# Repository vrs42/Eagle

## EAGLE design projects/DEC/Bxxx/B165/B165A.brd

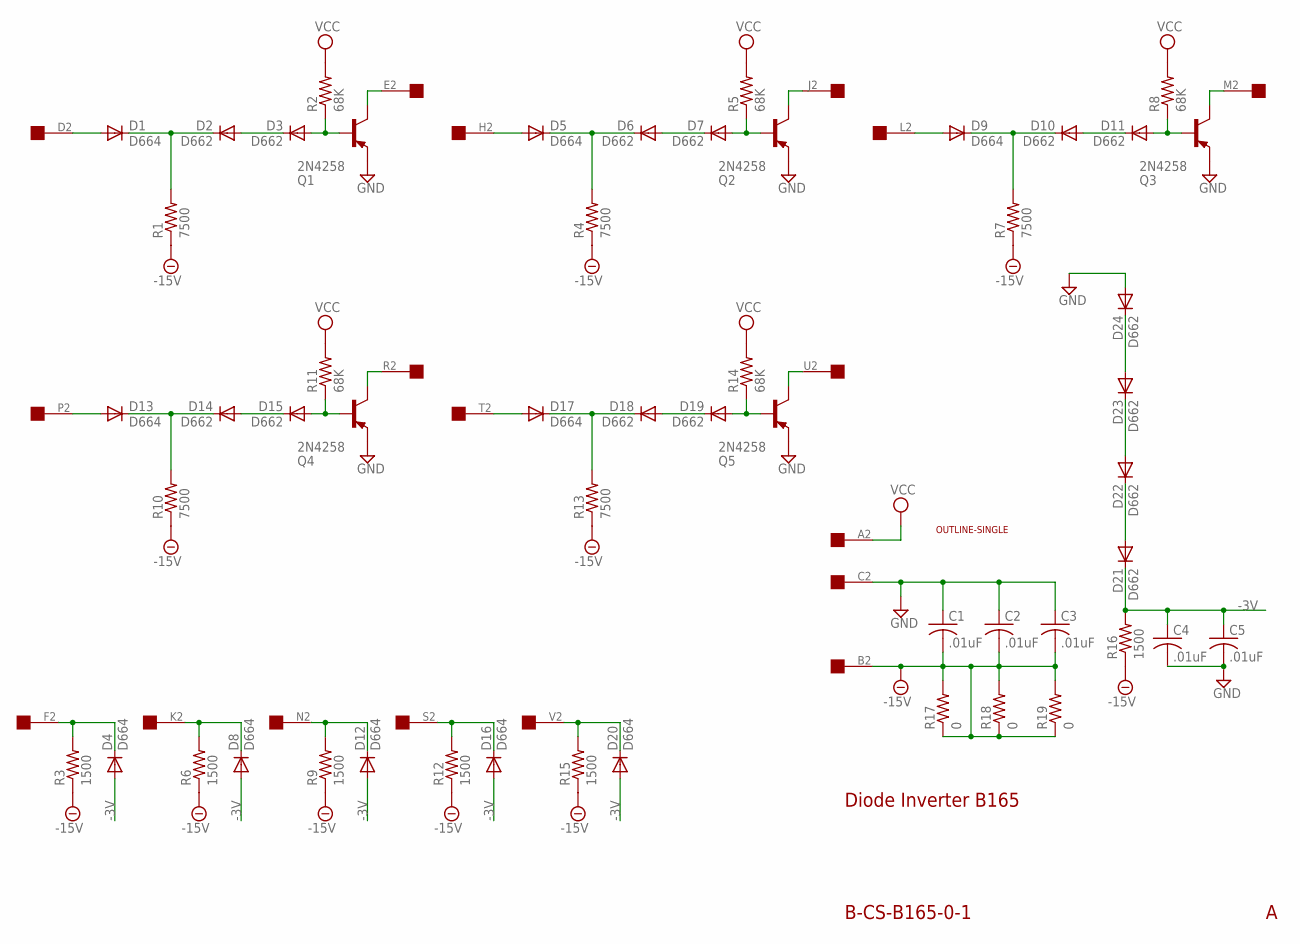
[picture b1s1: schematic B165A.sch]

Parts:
C1, C2, C3, C4, C5: .01uF; C063-025X075
D1, D4, D5, D8, D9, D12, D13, D16, D17, D20: D664; DO35-10
D2, D3, D6, D7, D10, D11, D14, D15, D18, D19, D21, D22, D23, D24: D662; DO35-10
Q1, Q2, Q3, Q4, Q5: 2N4258; TO5
R1, R4, R7, R10, R13: 7500; 0207/10
R2, R5, R8, R11, R14: 68K; 0207/10
R3, R6, R9, R12, R15, R16: 1500; 0207/10
R17, R18, R19: 0; 0207/10
U$1: OUTLINE-SINGLE; SINGLE
U$2: EDGE-1; EDGE-CON1

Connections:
-3V: C4.1, C5.1, D4.A, D8.A, D12.A, D16.A, D20.A, D21.C, R16.2
-15V: C1.2, C2.2, C3.2, R1.1, R3.1, R4.1, R6.1, R7.1, R9.1, R10.1, R12.1, R13.1, R15.1, R16.1, R17.1, R17.2, R18.1, R18.2, R19.1, R19.2, U$2.B2
GND: C1.1, C2.1, C3.1, C4.2, C5.2, D24.A, Q1.1 (E), Q2.1 (E), Q3.1 (E), Q4.1 (E), Q5.1 (E), U$2.C2
unnamed: D1.A, U$2.D2
unnamed: D1.C, D2.C, R1.2
unnamed: D2.A, D3.C
unnamed: D16.C, R12.2, U$2.S2
unnamed: D3.A, Q1.2 (B), R2.1
unnamed: Q1.3 (C), U$2.E2
unnamed: D4.C, R3.2, U$2.F2
unnamed: D8.C, R6.2, U$2.K2
unnamed: D12.C, R9.2, U$2.N2
unnamed: D5.A, U$2.H2
unnamed: D5.C, D6.C, R4.2
unnamed: D6.A, D7.C
unnamed: D17.A, U$2.T2
unnamed: D7.A, Q2.2 (B), R5.1
unnamed: Q2.3 (C), U$2.J2
unnamed: D9.A, U$2.L2
unnamed: D9.C, D10.C, R7.2
unnamed: D10.A, D11.C
unnamed: D17.C, D18.C, R13.2
unnamed: D11.A, Q3.2 (B), R8.1
unnamed: Q3.3 (C), U$2.M2
unnamed: D13.A, U$2.P2
unnamed: D13.C, D14.C, R10.2
unnamed: D14.A, D15.C
unnamed: D18.A, D19.C
unnamed: D15.A, Q4.2 (B), R11.1
unnamed: Q4.3 (C), U$2.R2
unnamed: D23.A, D24.C
unnamed: D22.A, D23.C
unnamed: D19.A, Q5.2 (B), R14.1
unnamed: D21.A, D22.C
unnamed: Q5.3 (C), U$2.U2
unnamed: D20.C, R15.2, U$2.V2
VCC: R2.2, R5.2, R8.2, R11.2, R14.2, U$2.A2

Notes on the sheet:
B-CS-B165-0-1
Diode Inverter B165

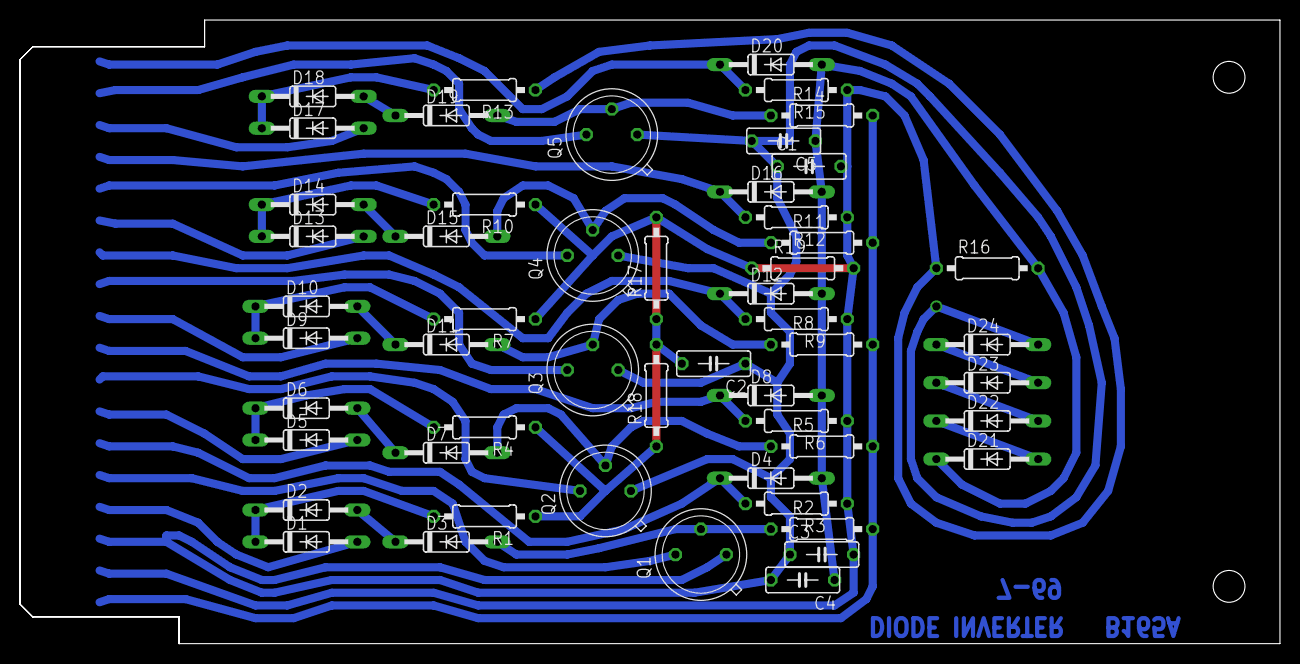
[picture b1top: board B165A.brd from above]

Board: 2 copper layers, 125.7 x 62.2 mm, 55 parts (0 on the bottom side), 37 nets.

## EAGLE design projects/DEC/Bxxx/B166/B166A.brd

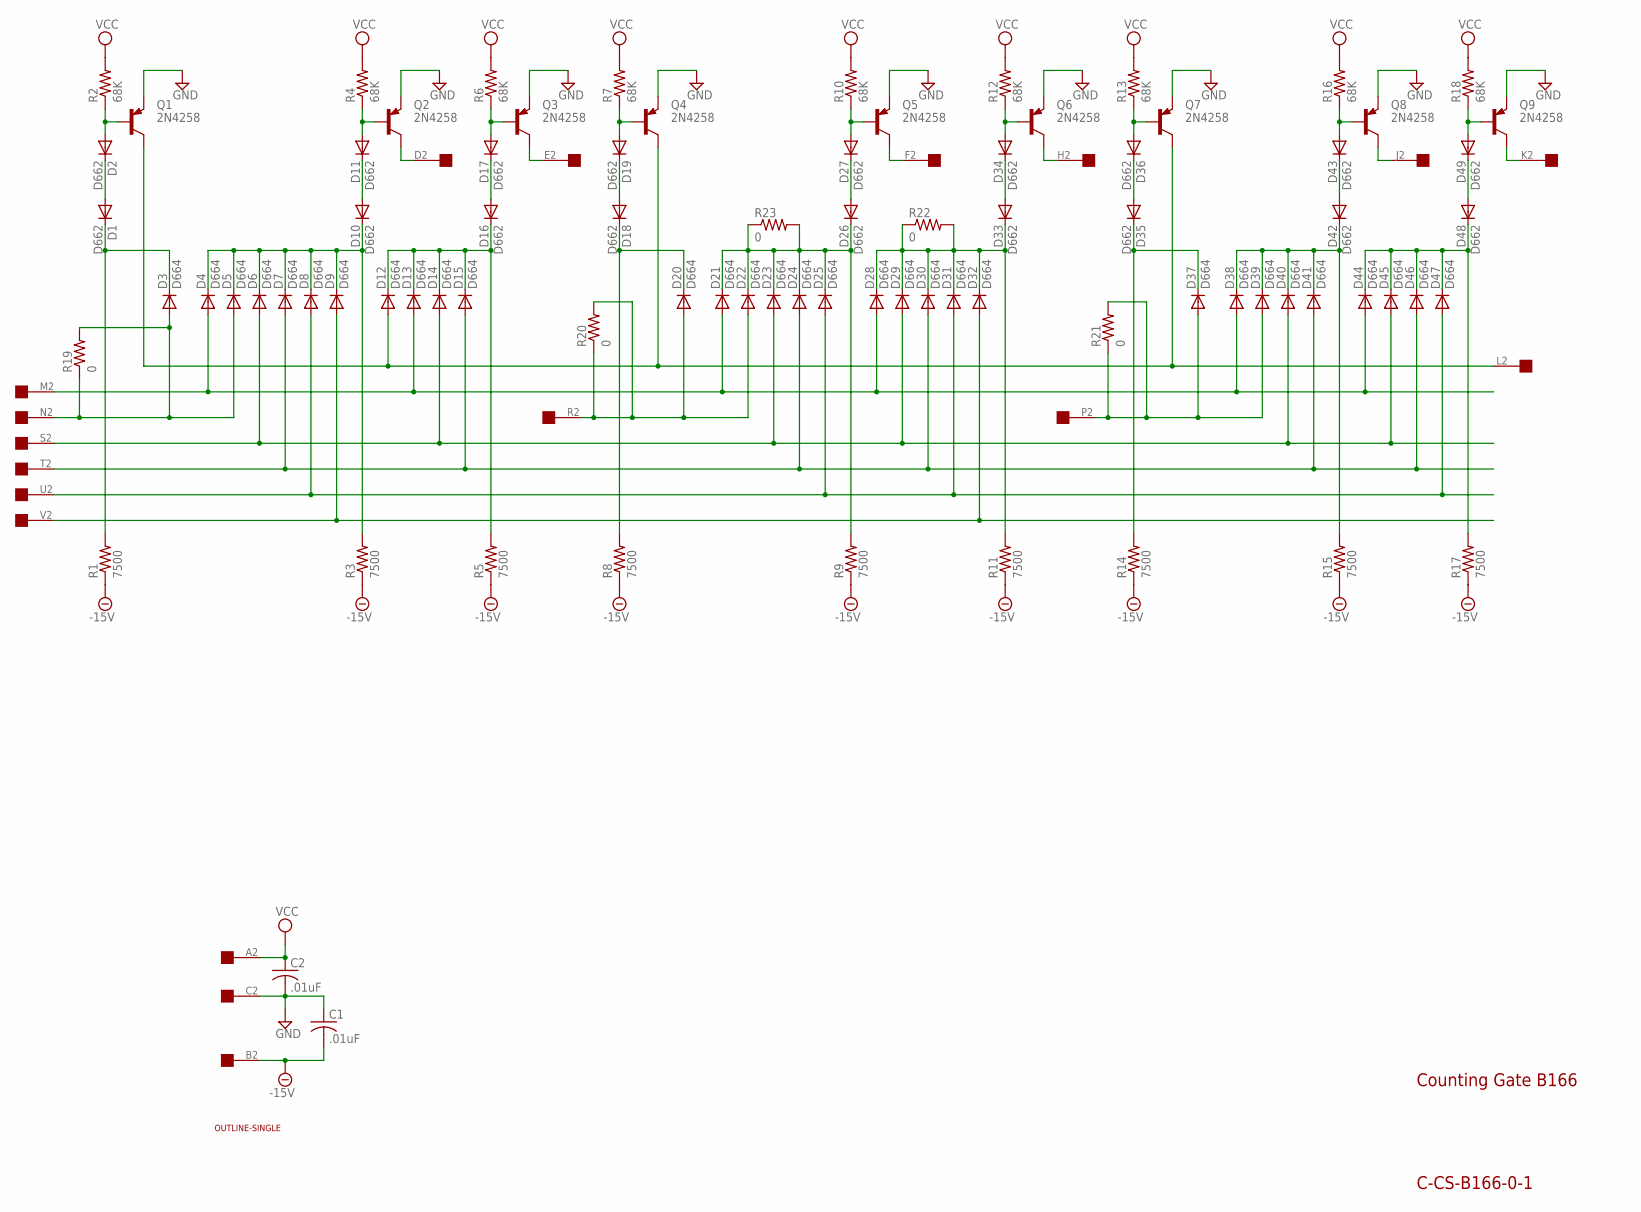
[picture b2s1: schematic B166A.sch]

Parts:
C1, C2: .01uF; C063-025X075
D1, D2, D10, D11, D16, D17, D18, D19, D26, D27, D33, D34, D35, D36, D42, D43, D48, D49: D662; DO35-10
D3, D4, D5, D6, D7, D8, D9, D12, D13, D14, D15, D20, D21, D22, D23, D24, D25, D28, D29, D30, D31, D32, D37, D38, D39, D40, D41, D44, D45, D46, D47: D664; DO35-10
Q1, Q2, Q3, Q4, Q5, Q6, Q7, Q8, Q9: 2N4258; TO5
R1, R3, R5, R8, R9, R11, R14, R15, R17: 7500; 0207/10
R2, R4, R6, R7, R10, R12, R13, R16, R18: 68K; 0207/10
R19, R20, R21, R22, R23: 0; 0207/10
U$1: OUTLINE-SINGLE; SINGLE
U$2: EDGE-1; EDGE-CON1

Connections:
-15V: C1.2, R1.1, R3.1, R5.1, R8.1, R9.1, R11.1, R14.1, R15.1, R17.1, U$2.B2
GND: C1.1, C2.2, Q1.1 (E), Q2.1 (E), Q3.1 (E), Q4.1 (E), Q5.1 (E), Q6.1 (E), Q7.1 (E), Q8.1 (E), Q9.1 (E), U$2.C2
unnamed: D2.A, Q1.2 (B), R2.1
unnamed: D1.A, D2.C
unnamed: D1.C, D3.C, R1.2
unnamed: D3.A, D5.A, R19.1, R19.2, U$2.N2
unnamed: D4.C, D5.C, D6.C, D7.C, D8.C, D9.C, D10.C, R3.2
unnamed: D12.A, Q1.3 (C), Q4.3 (C), Q7.3 (C), U$2.L2
unnamed: D4.A, D13.A, D21.A, D28.A, D38.A, D44.A, U$2.M2
unnamed: D8.A, D25.A, D31.A, D47.A, U$2.U2
unnamed: D7.A, D15.A, D24.A, D30.A, D41.A, D46.A, U$2.T2
unnamed: D11.A, Q2.2 (B), R4.1
unnamed: D9.A, D32.A, U$2.V2
unnamed: D6.A, D14.A, D23.A, D29.A, D40.A, D45.A, U$2.S2
unnamed: D10.A, D11.C
unnamed: Q2.3 (C), U$2.D2
unnamed: D19.A, Q4.2 (B), R7.1
unnamed: D12.C, D13.C, D14.C, D15.C, D16.C, R5.2
unnamed: D18.A, D19.C
unnamed: D18.C, D20.C, R8.2
unnamed: D20.A, D22.A, R20.1, R20.2, U$2.R2
unnamed: D21.C, D22.C, D23.C, D24.C, D25.C, D26.C, R9.2, R23.1, R23.2
unnamed: D17.A, Q3.2 (B), R6.1
unnamed: D16.A, D17.C
unnamed: Q3.3 (C), U$2.E2
unnamed: D27.A, Q5.2 (B), R10.1
unnamed: D26.A, D27.C
unnamed: Q5.3 (C), U$2.F2
unnamed: D28.C, D29.C, D30.C, D31.C, D32.C, D33.C, R11.2, R22.1, R22.2
unnamed: D34.A, Q6.2 (B), R12.1
unnamed: D33.A, D34.C
unnamed: Q6.3 (C), U$2.H2
unnamed: D36.A, Q7.2 (B), R13.1
unnamed: D35.A, D36.C
unnamed: D35.C, D37.C, R14.2
unnamed: D37.A, D39.A, R21.1, R21.2, U$2.P2
unnamed: D38.C, D39.C, D40.C, D41.C, D42.C, R15.2
unnamed: D43.A, Q8.2 (B), R16.1
unnamed: D42.A, D43.C
unnamed: Q8.3 (C), U$2.J2
unnamed: D44.C, D45.C, D46.C, D47.C, D48.C, R17.2
unnamed: D49.A, Q9.2 (B), R18.1
unnamed: D48.A, D49.C
unnamed: Q9.3 (C), U$2.K2
VCC: C2.1, R2.2, R4.2, R6.2, R7.2, R10.2, R12.2, R13.2, R16.2, R18.2, U$2.A2

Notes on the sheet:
C-CS-B166-0-1
Counting Gate B166

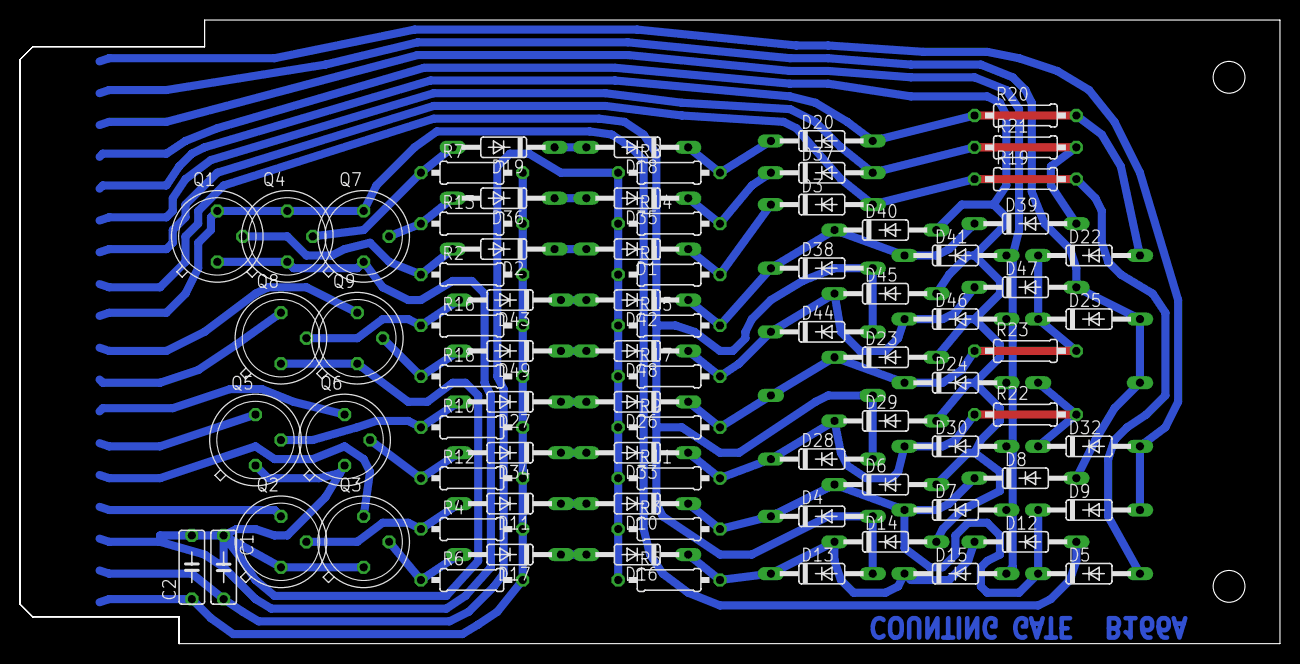
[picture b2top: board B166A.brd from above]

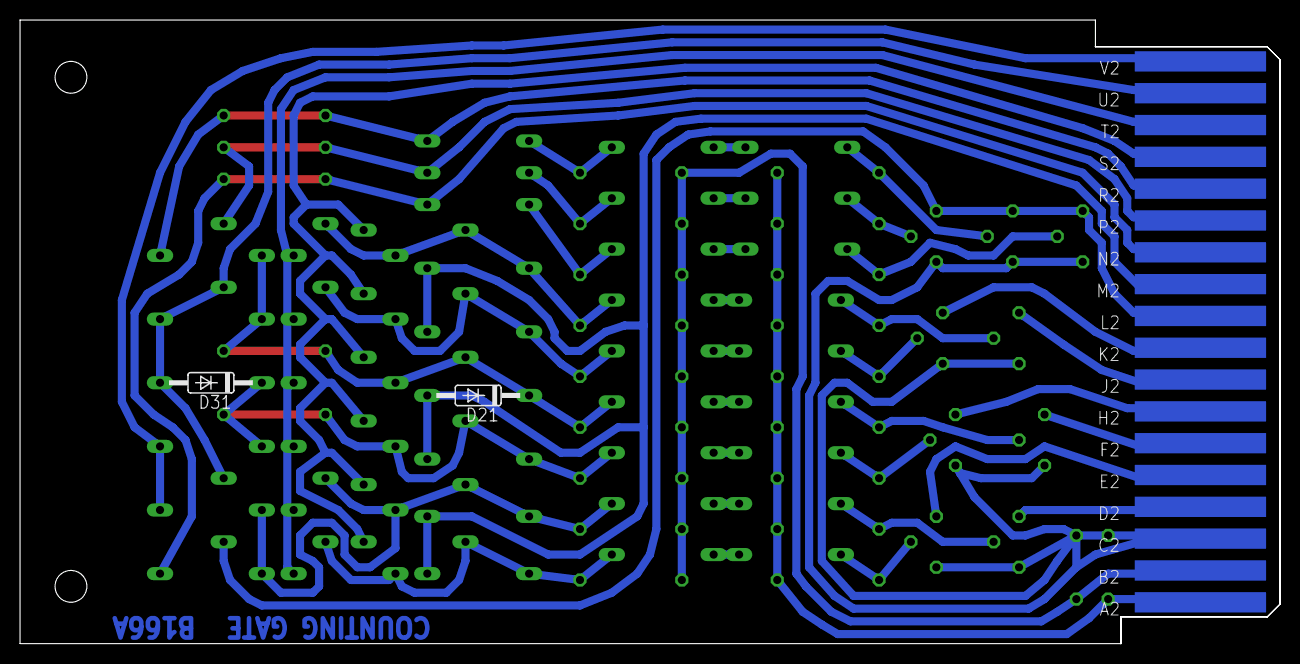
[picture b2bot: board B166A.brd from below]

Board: 2 copper layers, 125.7 x 62.2 mm, 85 parts (2 on the bottom side), 45 nets.

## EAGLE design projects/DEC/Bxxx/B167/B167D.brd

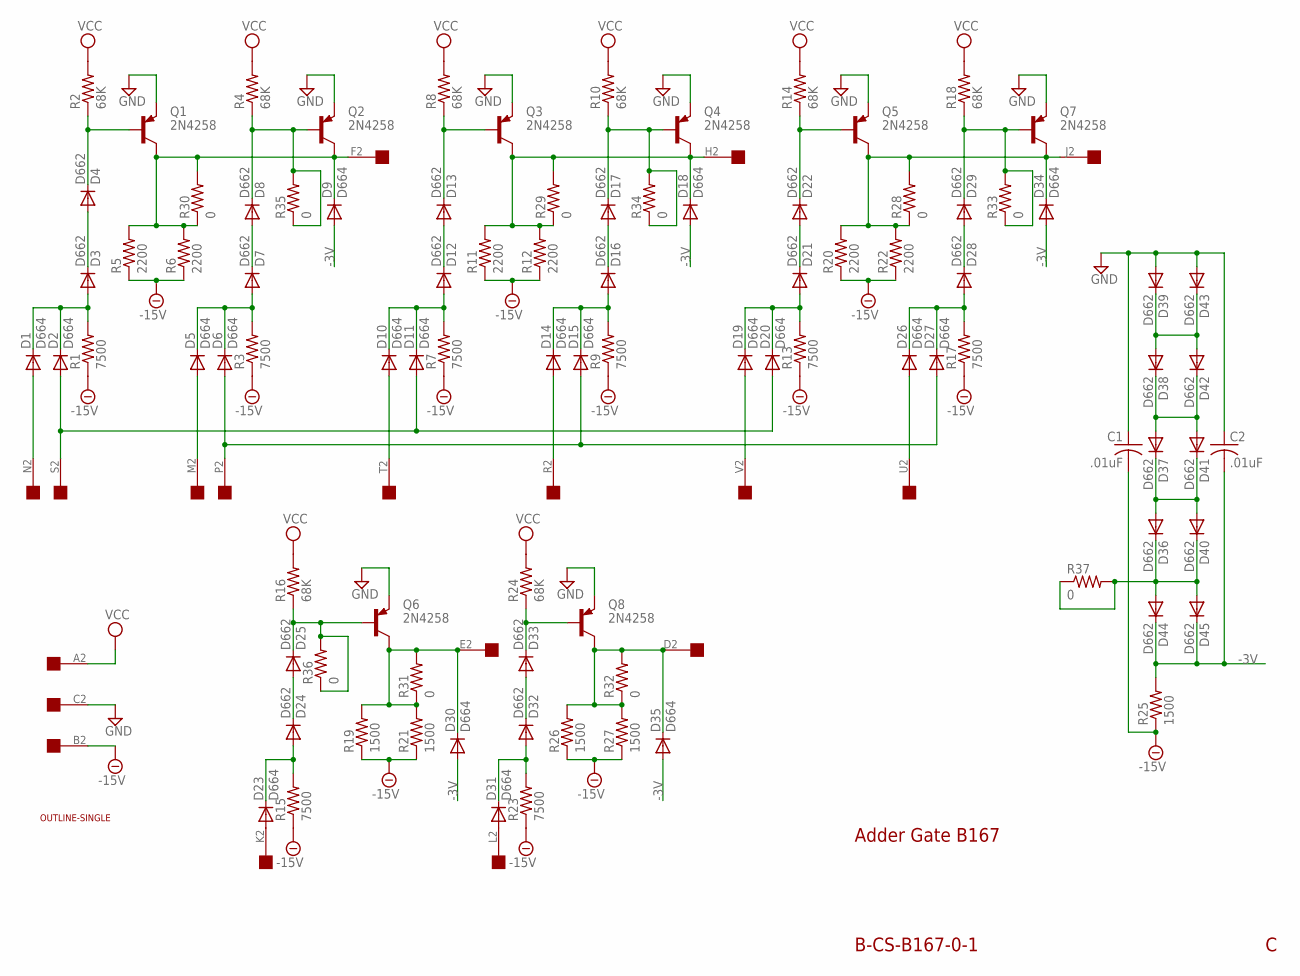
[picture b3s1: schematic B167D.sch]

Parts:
C1, C2: .01uF; C063-025X075
D1, D2, D5, D6, D9, D10, D11, D14, D15, D18, D19, D20, D23, D26, D27, D30, D31, D34, D35: D664; DO35-10
D3, D4, D7, D8, D12, D13, D16, D17, D21, D22, D24, D25, D28, D29, D32, D33, D36, D37, D38, D39, D40, D41, D42, D43, D44, D45: D662; DO35-10
Q1, Q2, Q3, Q4, Q5, Q6, Q7, Q8: 2N4258; TO5
R1, R3, R7, R9, R13, R15, R17, R23: 7500; 0207/10
R2, R4, R8, R10, R14, R16, R18, R24: 68K; 0207/10
R5, R6, R11, R12, R20, R22: 2200; 0207/10
R19, R21, R25, R26, R27: 1500; 0207/10
R28, R29, R30, R31, R32, R33, R34, R35, R36, R37: 0; 0207/10
U$1: OUTLINE-SINGLE; SINGLE
U$2: EDGE-1; EDGE-CON1

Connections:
-3V: C2.2, D9.A, D18.A, D30.A, D34.A, D35.A, D44.C, D45.C, R25.2
-15V: C1.2, R1.1, R3.1, R5.1, R6.1, R7.1, R9.1, R11.1, R12.1, R13.1, R15.1, R17.1, R19.1, R20.1, R21.1, R22.1, R23.1, R25.1, R26.1, R27.1, U$2.B2
GND: C1.1, C2.1, D39.A, D43.A, Q1.1 (E), Q2.1 (E), Q3.1 (E), Q4.1 (E), Q5.1 (E), Q6.1 (E), Q7.1 (E), Q8.1 (E), U$2.C2
unnamed: D4.C, Q1.2 (B), R2.1
unnamed: D3.C, D4.A
unnamed: D1.C, D2.C, D3.A, R1.2
unnamed: D8.C, Q2.2 (B), R4.1, R35.1, R35.2
unnamed: D7.C, D8.A
unnamed: D5.C, D6.C, D7.A, R3.2
unnamed: D9.C, Q1.3 (C), Q2.3 (C), R5.2, R6.2, R30.1, R30.2, U$2.F2
unnamed: D13.C, Q3.2 (B), R8.1
unnamed: D12.C, D13.A
unnamed: D10.C, D11.C, D12.A, R7.2
unnamed: D17.C, Q4.2 (B), R10.1, R34.1, R34.2
unnamed: D16.C, D17.A
unnamed: D14.C, D15.C, D16.A, R9.2
unnamed: D18.C, Q3.3 (C), Q4.3 (C), R11.2, R12.2, R29.1, R29.2, U$2.H2
unnamed: D22.C, Q5.2 (B), R14.1
unnamed: D21.C, D22.A
unnamed: D19.C, D20.C, D21.A, R13.2
unnamed: D29.C, Q7.2 (B), R18.1, R33.1, R33.2
unnamed: D28.C, D29.A
unnamed: D26.C, D27.C, D28.A, R17.2
unnamed: D34.C, Q5.3 (C), Q7.3 (C), R20.2, R22.2, R28.1, R28.2, U$2.J2
unnamed: D25.C, Q6.2 (B), R16.1, R36.1, R36.2
unnamed: D24.C, D25.A
unnamed: D23.C, D24.A, R15.2
unnamed: D30.C, Q6.3 (C), R19.2, R21.2, R31.1, R31.2, U$2.E2
unnamed: D33.C, Q8.2 (B), R24.1
unnamed: D32.C, D33.A
unnamed: D31.C, D32.A, R23.2
unnamed: D35.C, Q8.3 (C), R26.2, R27.2, R32.1, R32.2, U$2.D2
unnamed: D38.A, D39.C, D42.A, D43.C
unnamed: D23.A, U$2.K2
unnamed: D37.A, D38.C, D41.A, D42.C
unnamed: D31.A, U$2.L2
unnamed: D36.A, D37.C, D40.A, D41.C
unnamed: D1.A, U$2.N2
unnamed: D2.A, D11.A, D20.A, U$2.S2
unnamed: D36.C, D40.C, D44.A, D45.A, R37.1, R37.2
unnamed: D5.A, U$2.M2
unnamed: D6.A, D15.A, D27.A, U$2.P2
unnamed: D10.A, U$2.T2
unnamed: D14.A, U$2.R2
unnamed: D19.A, U$2.V2
unnamed: D26.A, U$2.U2
VCC: R2.2, R4.2, R8.2, R10.2, R14.2, R16.2, R18.2, R24.2, U$2.A2

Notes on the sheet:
B-CS-B167-0-1
Adder Gate B167

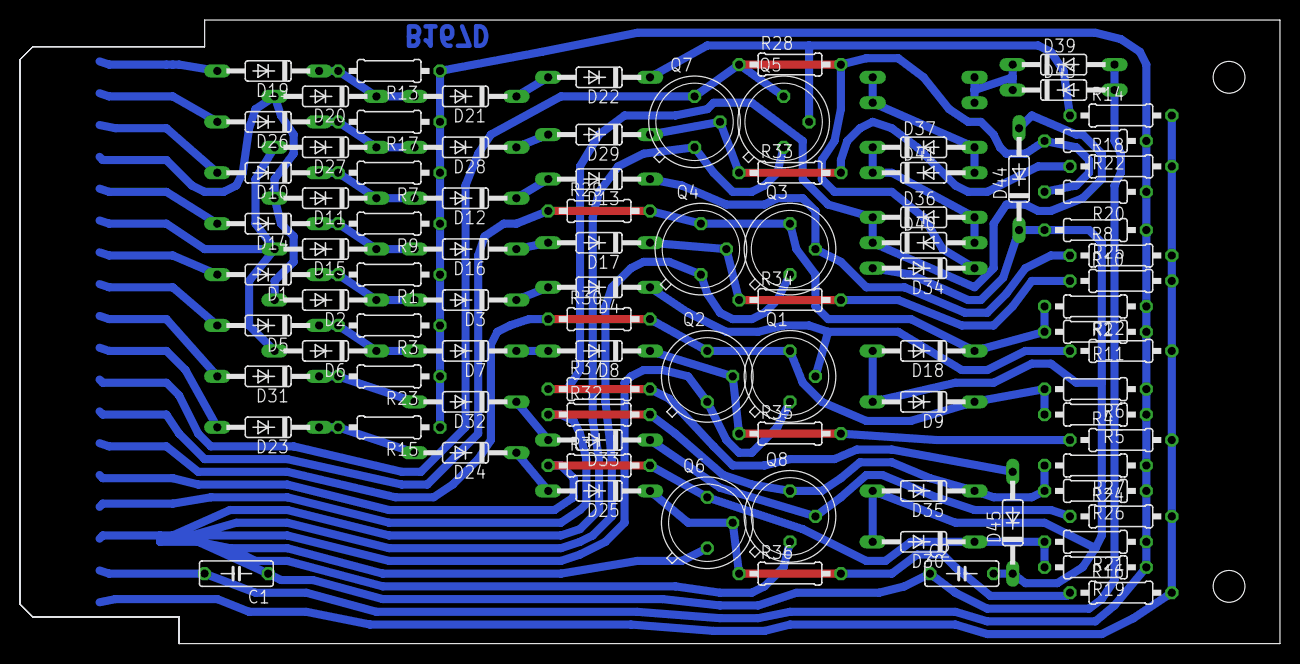
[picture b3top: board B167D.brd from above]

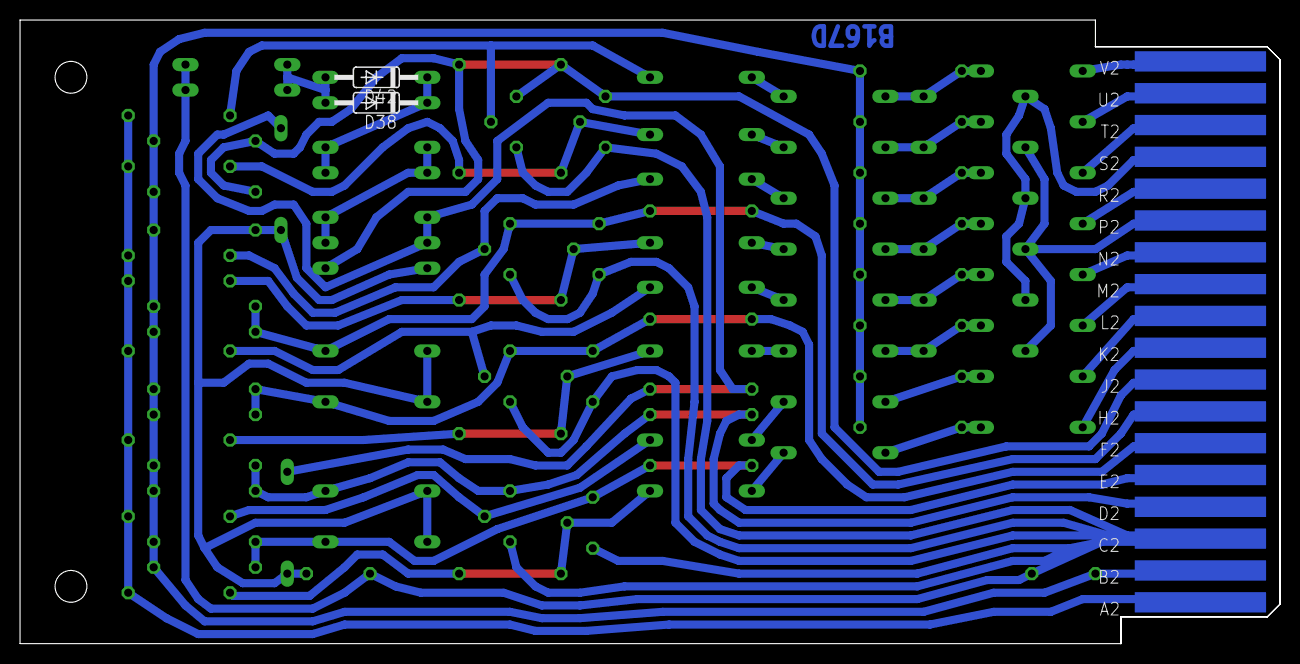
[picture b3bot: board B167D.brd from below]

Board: 2 copper layers, 125.7 x 62.2 mm, 94 parts (2 on the bottom side), 47 nets.

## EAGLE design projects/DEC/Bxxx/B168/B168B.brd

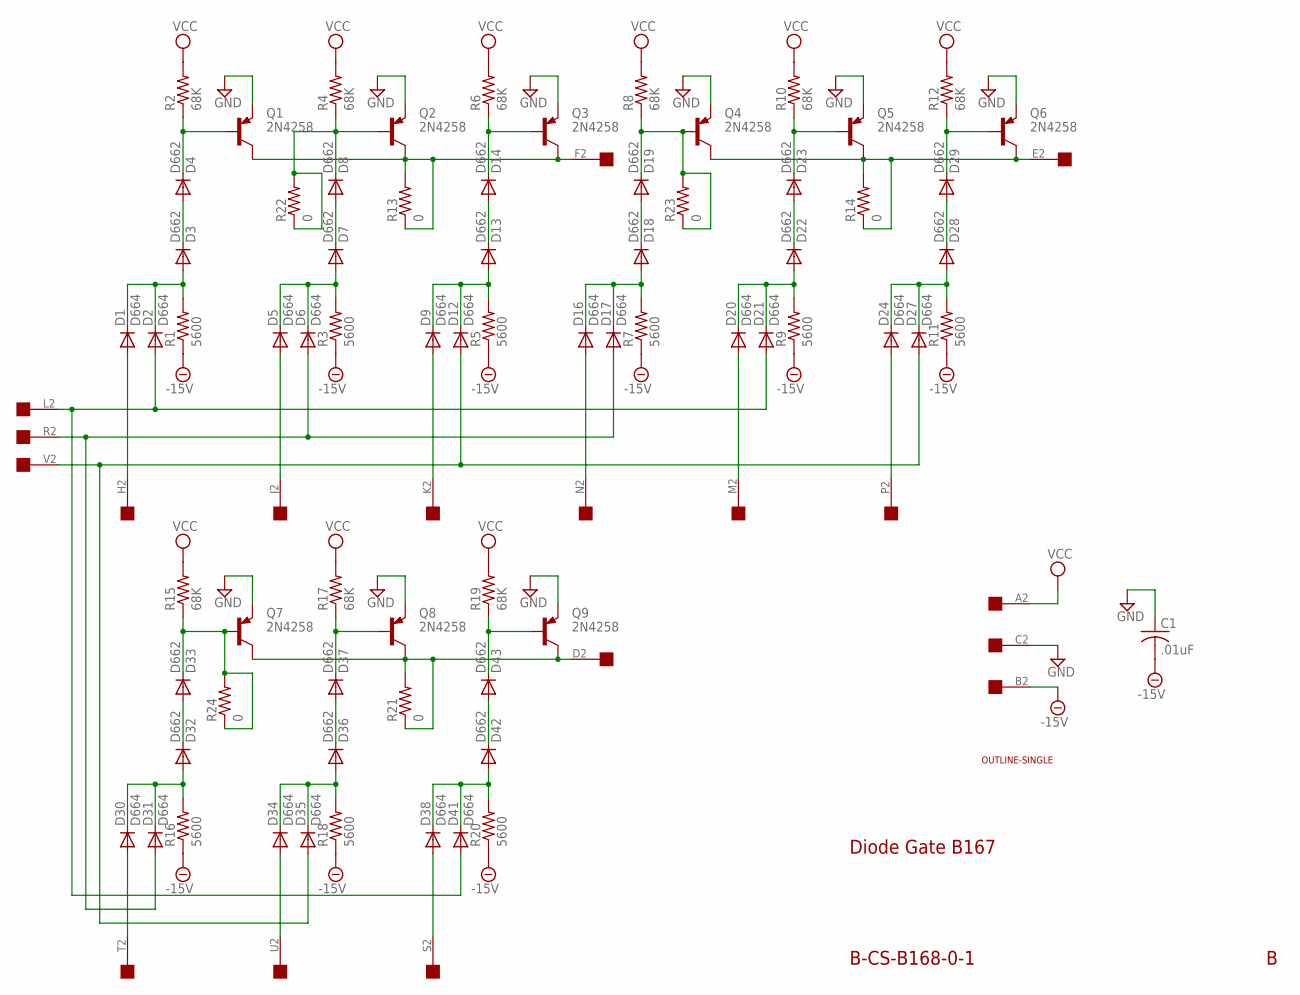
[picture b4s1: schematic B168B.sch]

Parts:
C1: .01uF; C063-025X075
D1, D2, D5, D6, D9, D12, D16, D17, D20, D21, D24, D27, D30, D31, D34, D35, D38, D41: D664; DO35-10
D3, D4, D7, D8, D13, D14, D18, D19, D22, D23, D28, D29, D32, D33, D36, D37, D42, D43: D662; DO35-10
Q1, Q2, Q3, Q4, Q5, Q6, Q7, Q8, Q9: 2N4258; TO5
R1, R3, R5, R7, R9, R11, R16, R18, R20: 5600; 0207/10
R2, R4, R6, R8, R10, R12, R15, R17, R19: 68K; 0207/10
R13, R14, R21, R22, R23, R24: 0; 0207/10
U$1: OUTLINE-SINGLE; SINGLE
U$2: EDGE-1; EDGE-CON1

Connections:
-15V: C1.2, R1.1, R3.1, R5.1, R7.1, R9.1, R11.1, R16.1, R18.1, R20.1, U$2.B2
GND: C1.1, Q1.1 (E), Q2.1 (E), Q3.1 (E), Q4.1 (E), Q5.1 (E), Q6.1 (E), Q7.1 (E), Q8.1 (E), Q9.1 (E), U$2.C2
unnamed: D4.C, Q1.2 (B), R2.1
unnamed: D3.C, D4.A
unnamed: D1.C, D2.C, D3.A, R1.2
unnamed: D8.C, Q2.2 (B), R4.1, R22.1, R22.2
unnamed: D7.C, D8.A
unnamed: D5.C, D6.C, D7.A, R3.2
unnamed: D5.A, U$2.J2
unnamed: D6.A, D17.A, D31.A, U$2.R2
unnamed: D14.C, Q3.2 (B), R6.1
unnamed: D13.C, D14.A
unnamed: D9.C, D12.C, D13.A, R5.2
unnamed: D9.A, U$2.K2
unnamed: D12.A, D27.A, D35.A, U$2.V2
unnamed: Q1.3 (C), Q2.3 (C), Q3.3 (C), R13.1, R13.2, U$2.F2
unnamed: D19.C, Q4.2 (B), R8.1, R23.1, R23.2
unnamed: D18.C, D19.A
unnamed: D16.C, D17.C, D18.A, R7.2
unnamed: D16.A, U$2.N2
unnamed: D33.C, Q7.2 (B), R15.1, R24.1, R24.2
unnamed: D23.C, Q5.2 (B), R10.1
unnamed: D22.C, D23.A
unnamed: D20.C, D21.C, D22.A, R9.2
unnamed: D20.A, U$2.M2
unnamed: D32.C, D33.A
unnamed: D29.C, Q6.2 (B), R12.1
unnamed: D28.C, D29.A
unnamed: D24.C, D27.C, D28.A, R11.2
unnamed: D24.A, U$2.P2
unnamed: D30.C, D31.C, D32.A, R16.2
unnamed: Q4.3 (C), Q5.3 (C), Q6.3 (C), R14.1, R14.2, U$2.E2
unnamed: D30.A, U$2.T2
unnamed: D37.C, Q8.2 (B), R17.1
unnamed: D36.C, D37.A
unnamed: D34.C, D35.C, D36.A, R18.2
unnamed: D1.A, U$2.H2
unnamed: D34.A, U$2.U2
unnamed: D43.C, Q9.2 (B), R19.1
unnamed: D42.C, D43.A
unnamed: D38.C, D41.C, D42.A, R20.2
unnamed: D38.A, U$2.S2
unnamed: Q7.3 (C), Q8.3 (C), Q9.3 (C), R21.1, R21.2, U$2.D2
unnamed: D2.A, D21.A, D41.A, U$2.L2
VCC: R2.2, R4.2, R6.2, R8.2, R10.2, R12.2, R15.2, R17.2, R19.2, U$2.A2

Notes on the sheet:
B-CS-B168-0-1
Diode Gate B167

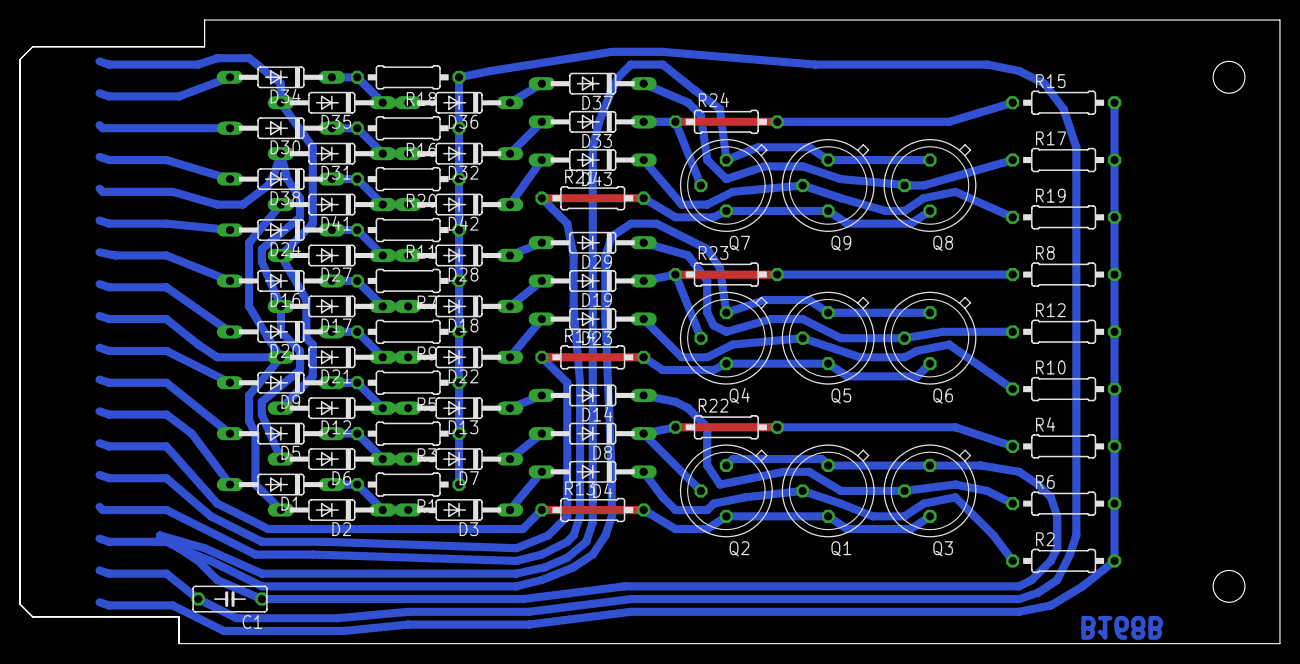
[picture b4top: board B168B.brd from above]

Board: 2 copper layers, 125.7 x 62.2 mm, 72 parts (0 on the bottom side), 45 nets.
